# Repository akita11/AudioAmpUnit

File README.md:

# AudioAmpUnit

Heroic社のオーディオアンプHT8693を使った10Wクラスのオーディオアンプです。（※電源電圧5Vでは3W程度） Groveコネクタからのオーディオ信号を、つないだスピーカで鳴らすことができます。イネーブル端子もGroveから制御できます。M5StackでDAC出力が使いやすいようなピン配置です。スピーカ接続端子の形状で2種類あります（プリント基板自体は両者で同一です）。なおGrove端子のピン配置は「Enable/AudioIn/VDD/GND」の順ですが、オーディオ入力とイネーブル信号の配置をソルダージャンパで入れ替え可能です。

いずれも、AudioIn信号に再生したい音声信号の電圧振幅をDAC出力から与えてください。Enabe=1とすればアンプがONとなり、Enable=0でアンプはOFFとなります。Enable信号は30kΩでプルアップされているので、未接続時・未使用時（マイコン側を入力端子に設定した場合など）にはアンプはONとなります。

## AudioAmpUnit（3.5mmJack)

φ3.5mmプラグのついたスピーカを接続可能です。ステレオスピーカではL側のみから出力されます。

## AudioAmpUnit（ねじ端子）

ねじ端子（VH3.96コネクタ）にスピーカを接続して使います。

基板形状が「[M5Stack用ADCユニット[U013]](https://www.switch-science.com/products/5221)」等と同一のため、そのケースを使うことができます。

## 設定の変更

- 動作モード: JP1を、中央-「D」をショート（デフォルトで基板パターンでショート）＝D級動作、中央-「AB」をショート＝AB級動作（D側の基板パターンをカットしてから使ってください）
- Groveコネクタのピン割当：JP3=Grove1番ピン(Gr1)。中央-「EN」（デフォルト）=Enable、中央-「AIN」=AudioIn（EN側の基板パターンをカットしてから使ってください）
- Groveコネクタのピン割当：JP4=Grove2番ピン(Gr2)。中央-「AIN」（デフォルト）=AudioIn、中央-「EN」=Enable（AudioIn側の基板パターンをカットしてから使ってください）

## Author

Junichi Akita (akita@ifdl.jp, @akita11)

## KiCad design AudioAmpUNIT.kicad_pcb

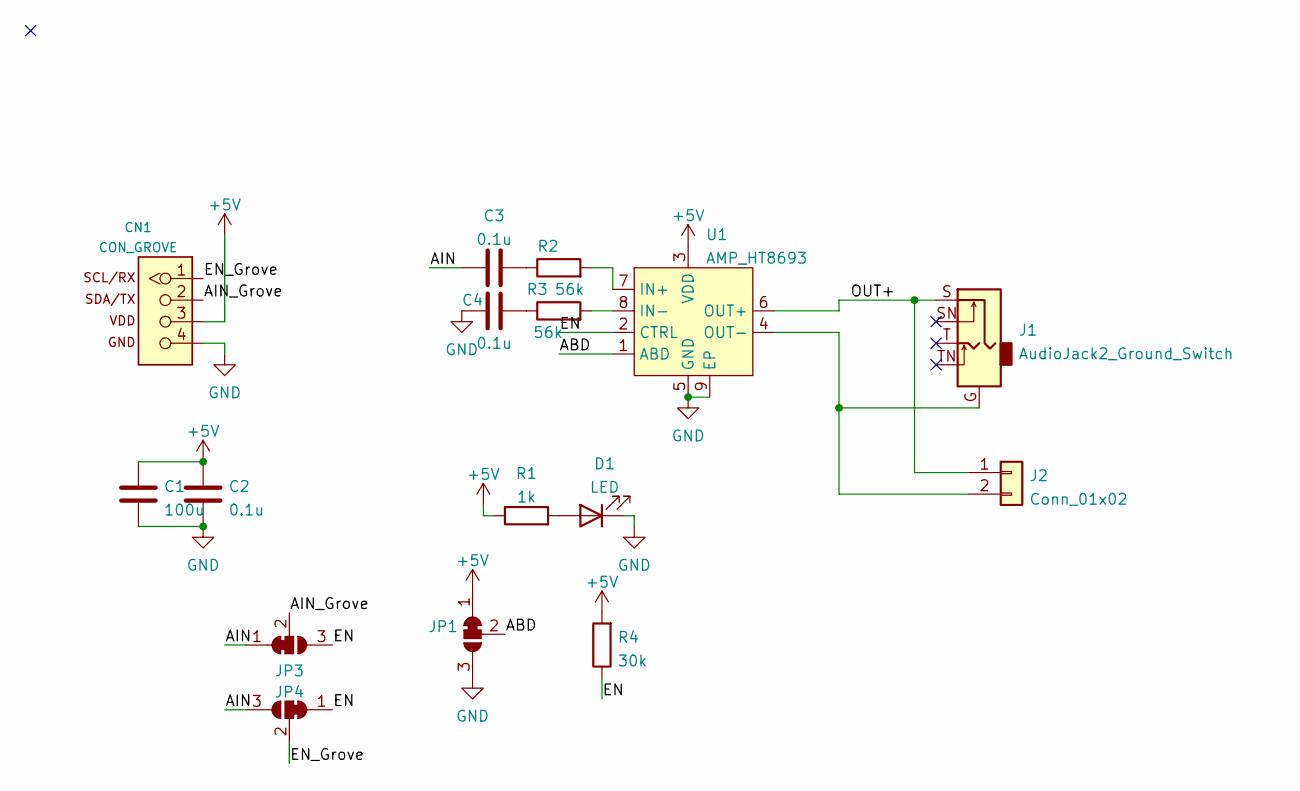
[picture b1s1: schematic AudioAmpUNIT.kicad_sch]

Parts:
C1: 100u; C_1206_3216Metric
C2, C3, C4: 0.1u; C_0603_1608Metric
CN1: CON_GROVE; CON_GROVE_H
D1: LED; LED_0603_1608Metric
J1: AudioJack2_Ground_Switch; CON_AJ-1780
J2: Conn_01x02; CON_HT396R_2P
JP1, JP3, JP4: SolderJumper_3_Bridged12; SolderJumper-3_P1.3mm_Bridged2Bar12_RoundedPad1.0x1.5mm
R1: 1k; R_0603_1608Metric
R2, R3: 56k; R_0603_1608Metric
R4: 30k; R_0603_1608Metric
U1: AMP_HT8693; SOP-8-EP_3.9x4.9mm_P1.27mm

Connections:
+5V: C1.2, C2.2, CN1.3, JP1.1 (A), R1.1, R4.2, U1.3 (VDD)
/ABD: JP1.2 (C), U1.1 (ABD)
/AIN: C3.1, JP3.1 (A), JP4.3 (B)
/AIN_Grove: CN1.2, JP3.2 (C)
/EN: JP3.3 (B), JP4.1 (A), R4.1, U1.2 (CTRL)
/EN_Grove: CN1.1, JP4.2 (C)
/OUT+: J1.S, J2.1, U1.6 (OUT+)
GND: C1.1, C2.1, C4.1, CN1.4, D1.1 (K), JP1.3 (B), U1.5 (GND), U1.9 (EP)
unnamed: C3.2, R2.1
unnamed: C4.2, R3.1
unnamed: D1.2 (A), R1.2
unnamed: J1.G, J2.2, U1.4 (OUT-)
unnamed: R2.2, U1.7 (IN+)
unnamed: R3.2, U1.8 (IN-)

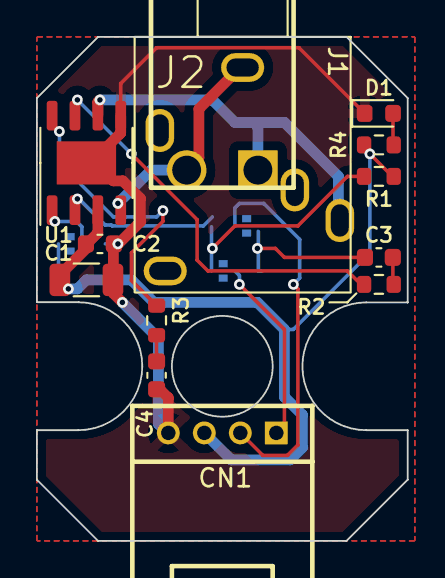
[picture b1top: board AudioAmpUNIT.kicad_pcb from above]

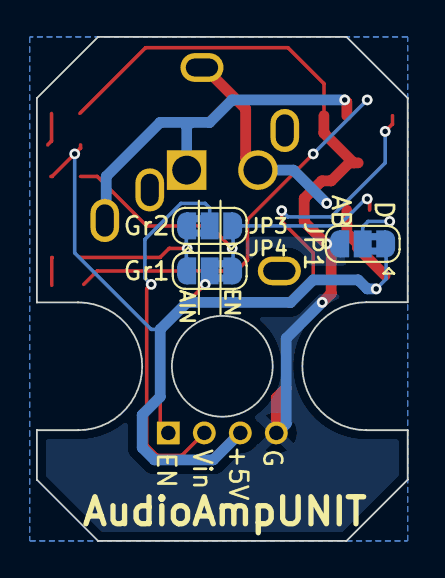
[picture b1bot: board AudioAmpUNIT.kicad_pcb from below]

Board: 2 copper layers, 20.6 x 28.0 mm, 16 parts (3 on the bottom side), 14 nets.

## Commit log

2023-02-27 add images
2023-02-28 add schematic
2023-02-28 README typo fix
2023-02-28 add KiCAD files
